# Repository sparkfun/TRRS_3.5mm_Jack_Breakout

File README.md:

SparkFun TRRS 3.5mm Jack Breakout
========================================

[*SparkFun TRRS 3.5mm Jack Breakout (BOB-11570)*](https://www.sparkfun.com/products/11570)

This breakout board makes it easy to add a TRRS jack to your prototype or project by breaking out each conductor to a standard 0.1" spaced header.
Repository Contents
-------------------

* **/Hardware** - Eagle design files (.brd, .sch)
* **/Production** - Production panel files (.brd)

Documentation
--------------
* **[SparkFun Fritzing repo](https://github.com/sparkfun/Fritzing_Parts)** - Fritzing diagrams for SparkFun products.
* **[SparkFun 3D Model repo](https://github.com/sparkfun/3D_Models)** - 3D models of SparkFun products. 

License Information
-------------------
This product is _**open source**_! 

The **hardware** is released under [Creative Commons ShareAlike 4.0 International](https://creativecommons.org/licenses/by-sa/4.0/).

Please use, reuse, and modify these files as you see fit. Please maintain attribution to SparkFun Electronics and release anything derivative under the same license.

Distributed as-is; no warranty is given.

- Your friends at SparkFun.

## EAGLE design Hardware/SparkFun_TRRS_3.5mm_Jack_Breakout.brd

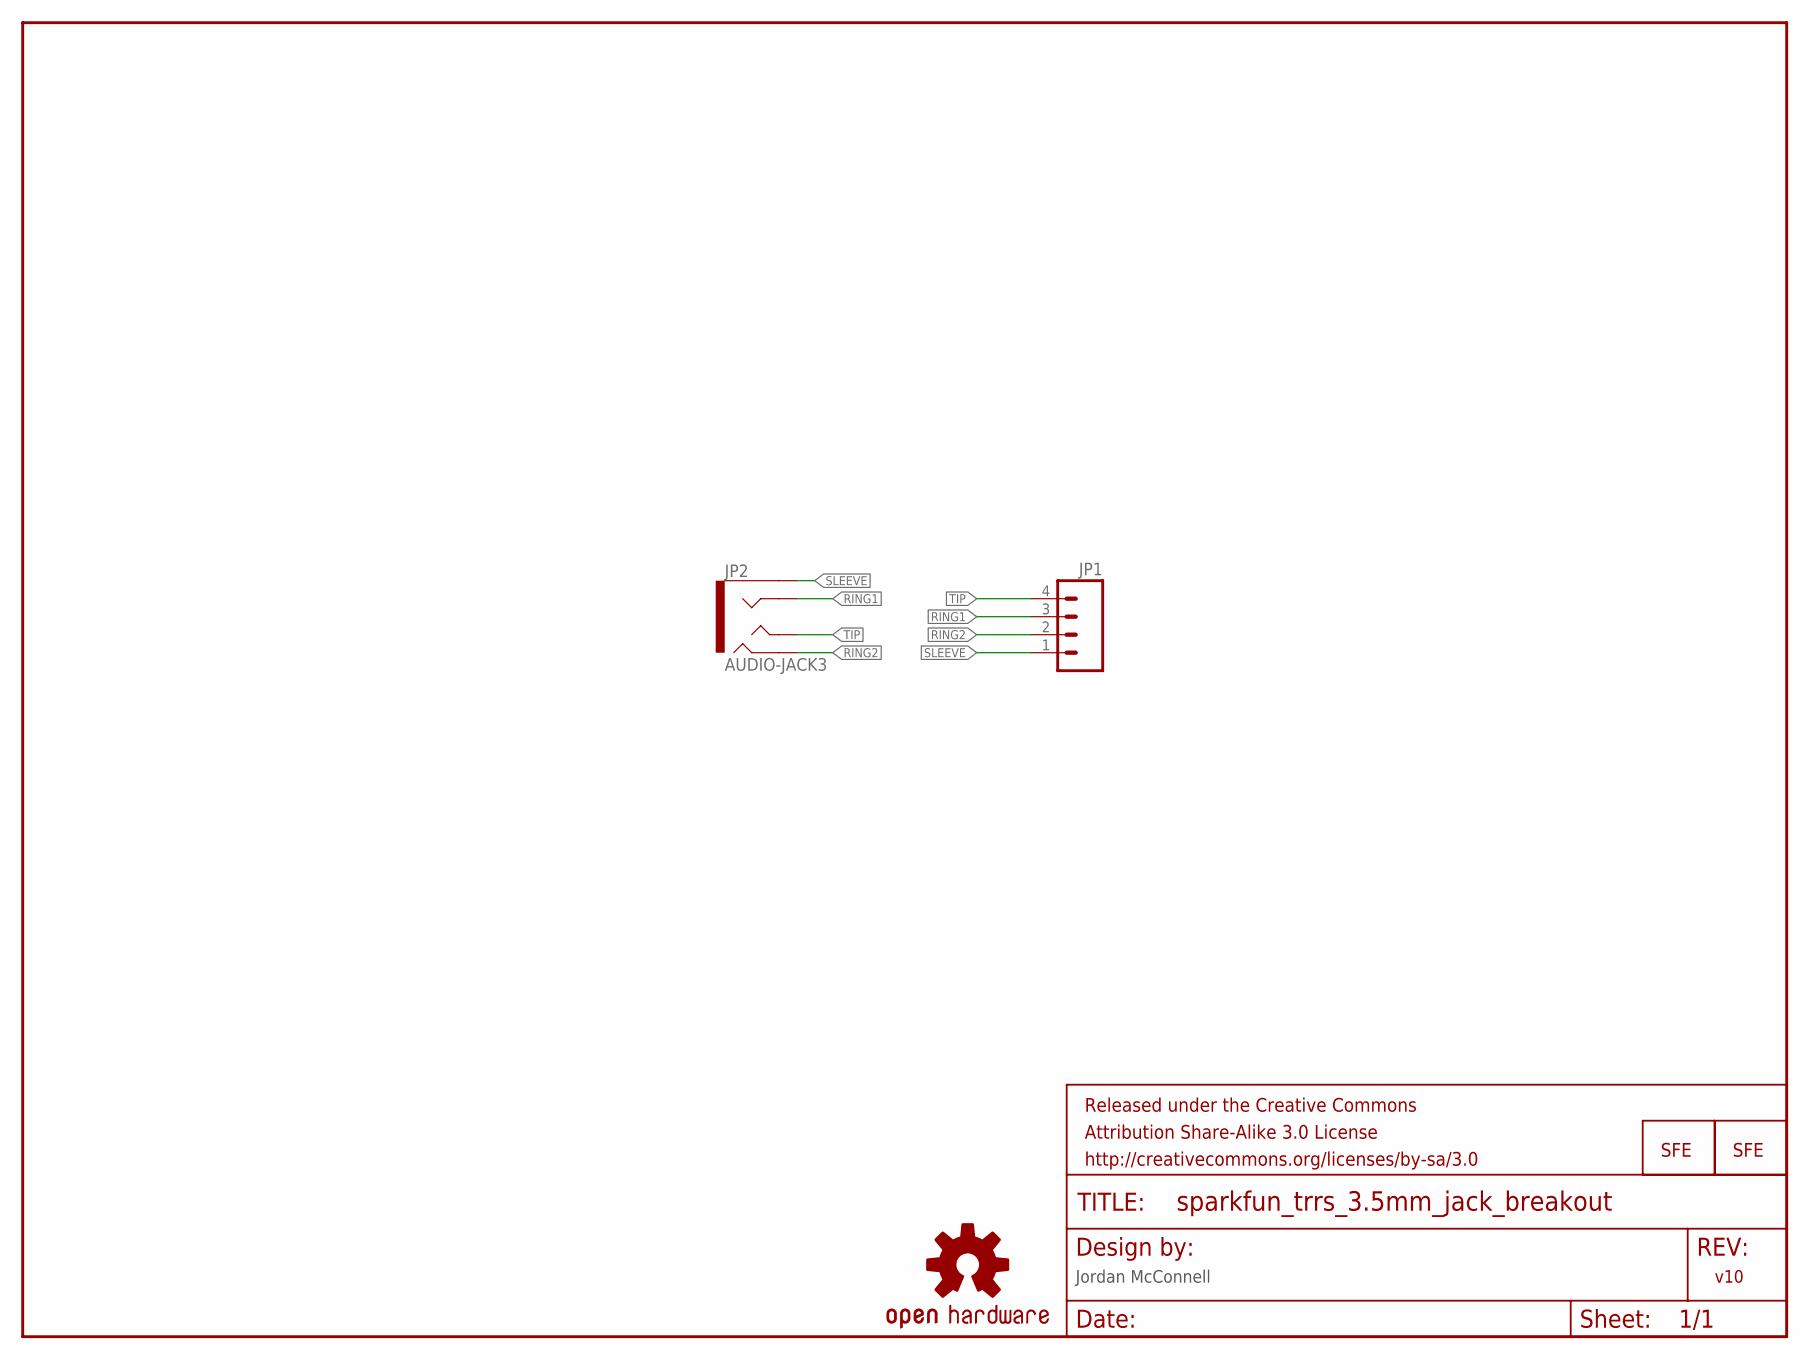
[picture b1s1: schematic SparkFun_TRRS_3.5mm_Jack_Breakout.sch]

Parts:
FRAME1: FRAME-LETTER; CREATIVE_COMMONS
JP1: M04PTH; 1X04
JP2: AUDIO-JACK3; AUDIO-JACK-TRRS-SMD
JP3, JP4: LOGO-SFESK; SFE-LOGO-FLAME
U$1: OSHW-LOGOS; OSHW-LOGO-S

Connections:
RING1: JP1.3, JP2.RING1
RING2: JP1.2, JP2.RING2
SLEEVE: JP1.1, JP2.EARTH
TIP: JP1.4, JP2.TIP

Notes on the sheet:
Jordan McConnell
v10

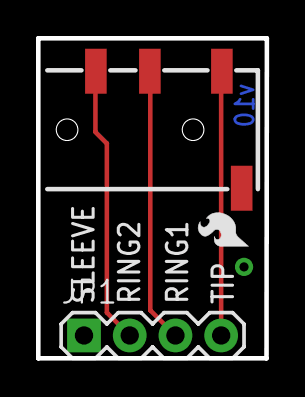
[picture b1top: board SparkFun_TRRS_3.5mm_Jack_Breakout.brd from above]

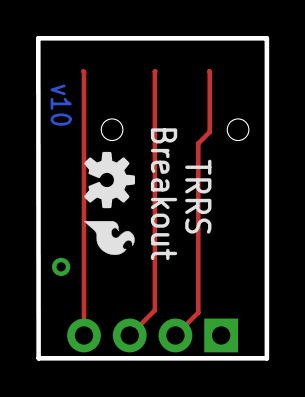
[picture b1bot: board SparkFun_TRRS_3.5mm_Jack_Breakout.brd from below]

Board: 2 copper layers, 12.7 x 17.8 mm, 6 parts (2 on the bottom side), 4 nets.

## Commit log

2015-05-05 Adding hardware files, updating README

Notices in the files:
parts and their libraries:
SparkFun-Aesthetics: Licensing: CC v3.0 Share-Alike You are welcome to use this library for commercial purposes.
SparkFun-Aesthetics: Released under the Creative Commons Attribution Share-Alike 3.0 License
SparkFun-Aesthetics: http://creativecommons.org/licenses/by-sa/3.0
